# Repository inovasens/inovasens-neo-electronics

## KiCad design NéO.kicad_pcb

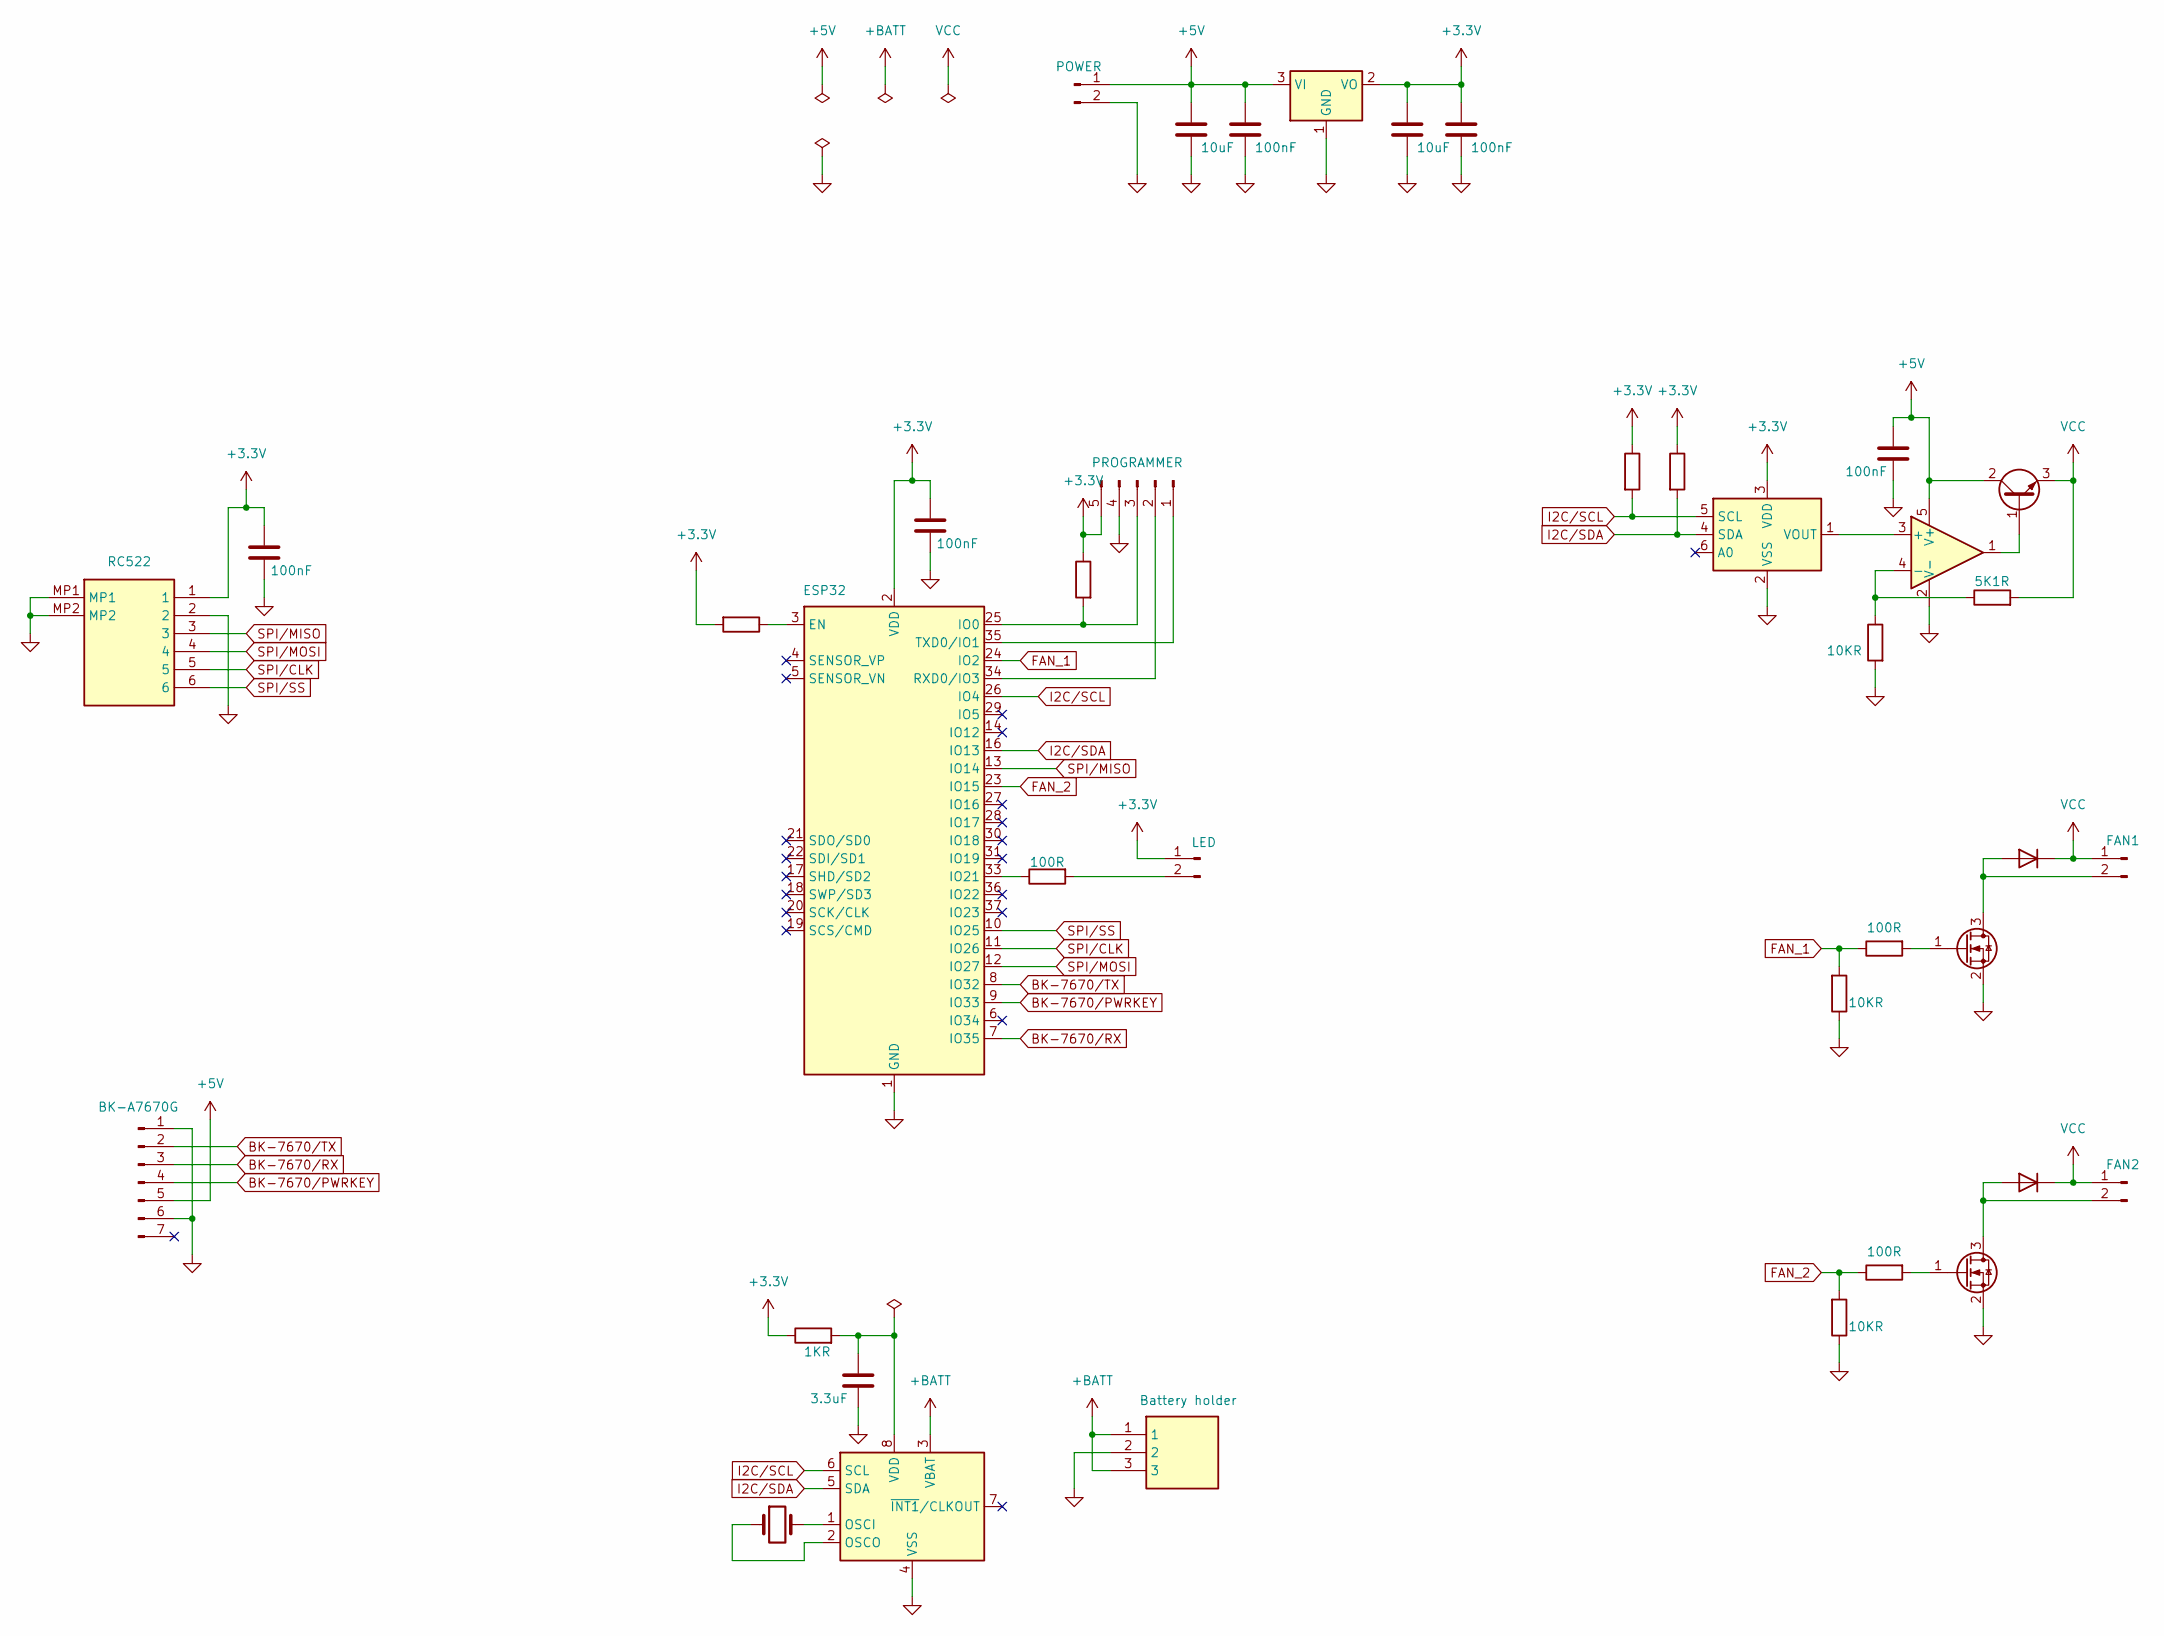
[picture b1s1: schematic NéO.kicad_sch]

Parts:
C2, C4, C6, C8, C9: 100nF; C_0603_1608Metric_Pad1.08x0.95mm_HandSolder
C3: 3.3uF; C_0603_1608Metric_Pad1.08x0.95mm_HandSolder
C5, C7: 10uF; C_0603_1608Metric_Pad1.08x0.95mm_HandSolder
D1, D2: D; D_SOD-123
J1: RC522; F51L1A7H111006
J2: BK-A7670G; PinHeader_1x07_P2.54mm_Vertical
J3: POWER; JST_PH_S2B-PH-K_1x02_P2.00mm_Horizontal
J4: Battery holder; Harwin_S8201-46R
J5: PROGRAMMER; PinHeader_1x05_P2.54mm_Vertical
J6: LED; JST_PH_S2B-PH-K_1x02_P2.00mm_Horizontal
J7: FAN2; JST_PH_S2B-PH-K_1x02_P2.00mm_Horizontal
J9: FAN1; JST_PH_S2B-PH-K_1x02_P2.00mm_Horizontal
Q1, Q2: IRLML6244; SOT-23
Q3: BCV71; SOT-23
R1, R6, R7, R8, R9, R10, R11: 10KR; R_0603_1608Metric_Pad0.98x0.95mm_HandSolder
R2: 1KR; R_0603_1608Metric_Pad0.98x0.95mm_HandSolder
R5, R12, R13: 100R; R_0603_1608Metric_Pad0.98x0.95mm_HandSolder
R14: 5K1R; R_0603_1608Metric_Pad0.98x0.95mm_HandSolder
U1: ESP32; ESP32-WROOM-32D
U2: PCF8523T; SOIC-8_3.9x4.9mm_P1.27mm
U3: LD1117S33TR_SOT223; SOT-223-3_TabPin2
U4: MCP4706; SOT-23-6
U5: AD8591ARTZ-REEL7; SOT-23-5
Y1: Crystal; Crystal_SMD_3215-2Pin_3.2x1.5mm

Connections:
+3.3V: C2.1, C4.1, C7.1, C8.1, J1.1, J5.5, J6.1, R1.2, R2.1, R6.1, R7.1, R8.1, U1.2 (VDD), U3.2 (VO), U4.3 (VDD)
+5V: C5.1, C6.1, C9.1, J2.5, J3.1, Q3.2 (C), U3.3 (VI), U5.5 (V+)
+BATT: J4.1, J4.3, U2.3 (VBAT)
BK-7670/PWRKEY: J2.4, U1.9 (IO33)
BK-7670/RX: J2.3, U1.7 (IO35)
BK-7670/TX: J2.2, U1.8 (IO32)
FAN_1: R9.2, R12.1, U1.24 (IO2)
FAN_2: R10.2, R13.1, U1.23 (IO15)
GND: C2.2, C3.2, C4.2, C5.2, C6.2, C7.2, C8.2, C9.2, J1.2, J1.MP1, J1.MP2, J2.1, J2.6, J3.2, J4.2, J5.4, Q1.2 (S), Q2.2 (S), R9.1, R10.1, R11.2, U1.1 (GND), U1.15 (GND), U1.38 (GND), U1.39 (GND), U2.4 (VSS), U3.1 (GND), U4.2 (VSS), U5.2 (V-)
I2C/SCL: R7.2, U1.26 (IO4), U2.6 (SCL), U4.5 (SCL)
I2C/SDA: R8.2, U1.16 (IO13), U2.5 (SDA), U4.4 (SDA)
unnamed: D1.2 (A), J9.2, Q1.3 (D)
unnamed: D2.2 (A), J7.2, Q2.3 (D)
unnamed: J5.1, U1.35 (TXD0/IO1)
unnamed: J5.2, U1.34 (RXD0/IO3)
unnamed: J5.3, R6.2, U1.25 (IO0)
unnamed: J6.2, R5.2
unnamed: Q1.1 (G), R12.2
unnamed: Q2.1 (G), R13.2
unnamed: Q3.1 (B), U5.1
unnamed: R1.1, U1.3 (EN)
unnamed: R5.1, U1.33 (IO21)
unnamed: U2.1 (OSCI), Y1.2
unnamed: U2.2 (OSCO), Y1.1
unnamed: C3.1, R2.2, U2.8 (VDD)
unnamed: U4.1 (VOUT), U5.3 (+)
unnamed: R11.1, R14.1, U5.4 (-)
SPI/CLK: J1.5, U1.11 (IO26)
SPI/MISO: J1.3, U1.13 (IO14)
SPI/MOSI: J1.4, U1.12 (IO27)
SPI/SS: J1.6, U1.10 (IO25)
VCC: D1.1 (K), D2.1 (K), J7.1, J9.1, Q3.3 (E), R14.2

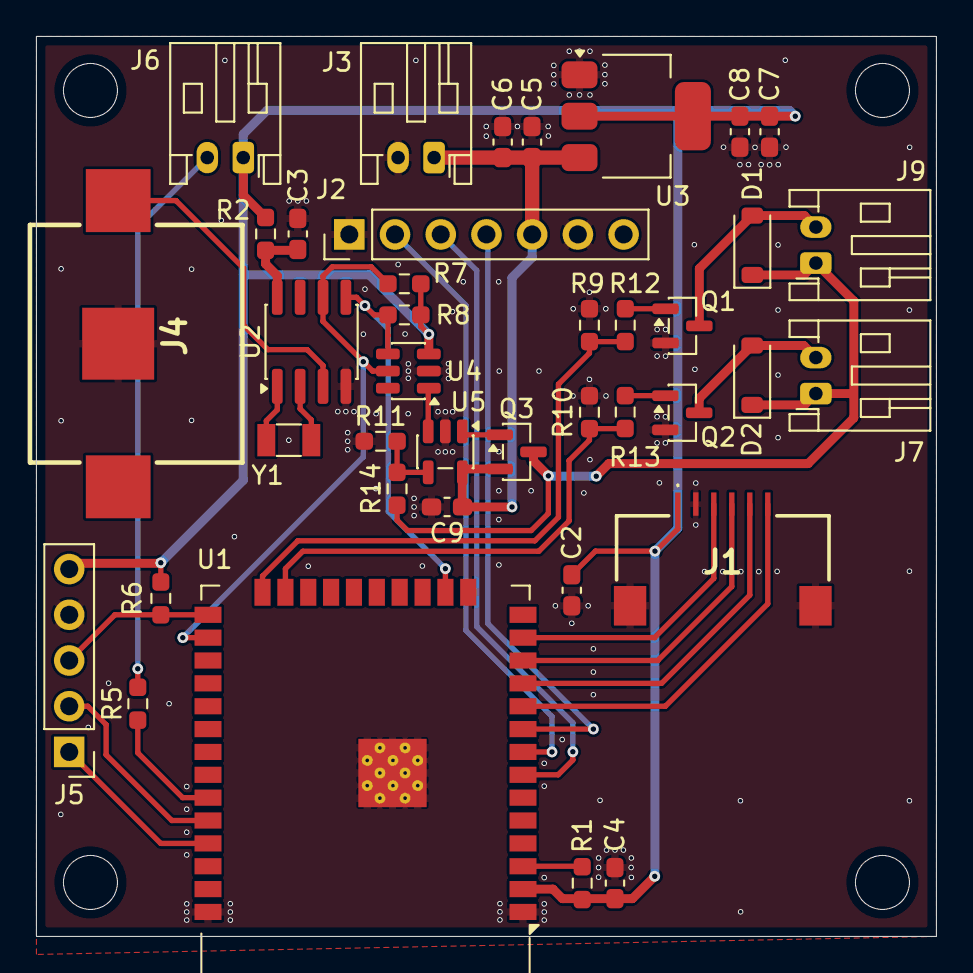
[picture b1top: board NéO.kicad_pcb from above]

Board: 2 copper layers, 50.0 x 50.0 mm, 39 parts (0 on the bottom side), 32 nets.

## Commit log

2025-11-28 Mise en gestion de configuration.
2025-11-28 Mise à jour des exclusions.
2025-12-02 Mise à jour des fichiers 3D.
2025-12-03 Mise à jour des SKU des composants.
2025-12-03 Mise à jour du fichier 3D du model GSM.
